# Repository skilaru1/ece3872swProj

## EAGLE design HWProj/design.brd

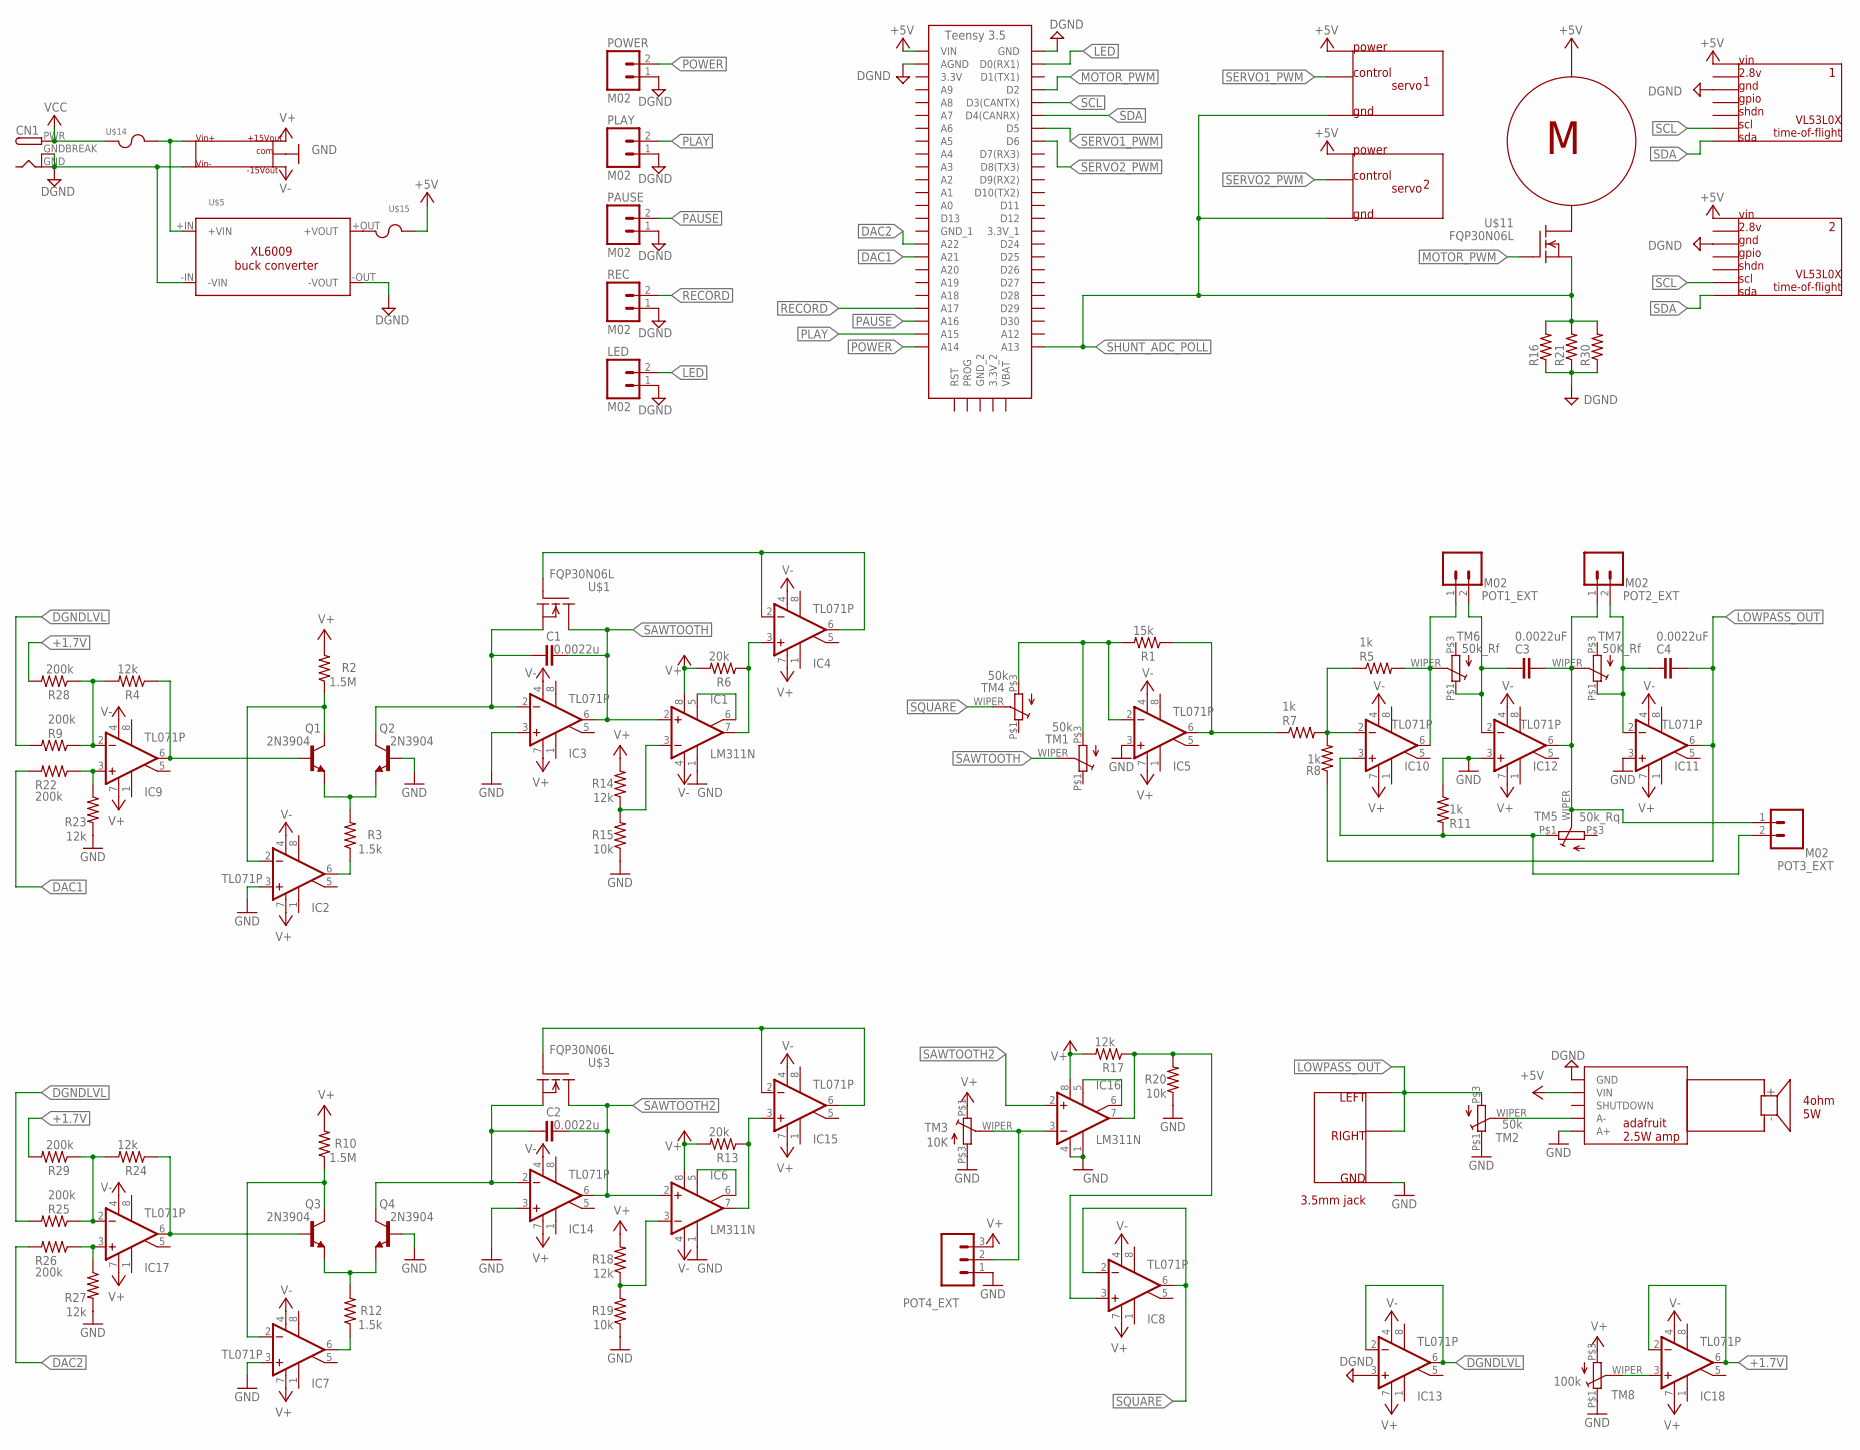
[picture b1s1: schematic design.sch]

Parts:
C1, C2: 0.0022u; CAP-PTH-5MM
C3, C4: 0.0022uF; CAP-PTH-5MM
CN1: DCBARRELPTH; DCJACK_2MM_PTH
IC1, IC6, IC16: LM311N; DIL08
IC2, IC3, IC4, IC5, IC7, IC8, IC9, IC10, IC11, IC12, IC13, IC14, IC15, IC17, IC18: TL071P; DIL08
LED: M02; 1X02
PAUSE: M02; 1X02
PLAY: M02; 1X02
POT1_EXT, POT2_EXT, POT3_EXT: M02; 1X02
POT4_EXT: M03; 1X03
POWER: M02; 1X02
Q1, Q2, Q3, Q4: 2N3904; TO92
R1: 15k; AXIAL-0.3
R2, R10: 1.5M; AXIAL-0.3
R3, R12: 1.5k; AXIAL-0.3
R4, R14, R17, R18, R23, R24, R27: 12k; AXIAL-0.3
R5, R7, R8, R11: 1k; AXIAL-0.3
R6, R13: 20k; AXIAL-0.3
R9, R22, R25, R26, R28, R29: 200k; AXIAL-0.3
R15, R19, R20: 10k; AXIAL-0.3
R16, R21, R30: RESISTORAXIAL-0.3; AXIAL-0.3
REC: M02; 1X02
TM1, TM2, TM4: 50k; 3386_TRI
TM3: 10K; 3386_TRI
TM5: 50k_Rq; 3386_TRI
TM6: 50k_Rf; 3386_TRI
TM7: 50K_Rf; 3386_TRI
TM8: 100k; 3386_TRI
U$1, U$3, U$11: FQP30N06L; TO-220
U$2: PAM8302A_ADAFRUIT
U$4: TEENSY_3.5_EXT
U$5: DC/DC-STEP-DOWN-XL6009; DC/DC-STEP-UP-XL6009
U$6: 3.5MM_AUDIO_JACK
U$7: +/-15V_BOOST_CONVERTER
U$8, U$9: SERVO_3PIN_HEADER
U$10: 3872_MOTOR
U$12, U$13: VL53L0X
U$14, U$15: FUSE_5X20MM; 0751.0110

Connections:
+1.7V: IC18.2 (-IN), IC18.6 (OUT), R28.P$2 (2), R29.P$2 (2)
+5V: U$2.VIN, U$4.VIN, U$8.POWER, U$9.POWER, U$10.+, U$12.VIN, U$13.VIN, U$15.R1 (2), U$15.R2 (2)
BANDPASS_OUT: C3.1, IC12.6 (OUT), POT2_EXT.1, POT3_EXT.1, TM5.WIPER (S), TM7.WIPER (S)
COMP_SQ_OUT: IC8.3 (+IN), IC16.7 (OUT), R17.P$1 (1), R20.P$2 (2)
DAC1: R22.P$2 (2), U$4.A21
DAC2: R26.P$2 (2), U$4.A22
DGND: CN1.GND, CN1.GNDBREAK, IC13.3 (+IN), LED.1, PAUSE.1, PLAY.1, POWER.1, R16.P$1 (1), R21.P$1 (1), R30.P$1 (1), REC.1, U$2.GND, U$4.AGND, U$4.GND, U$5.-IN (-VIN), U$5.-OUT (-VOUT), U$7.1, U$12.GND, U$13.GND
DGNDLVL: IC13.2 (-IN), IC13.6 (OUT), R9.P$2 (2), R25.P$2 (2)
GND: IC1.1 (GND), IC2.3 (+IN), IC3.3 (+IN), IC5.3 (+IN), IC6.1 (GND), IC7.3 (+IN), IC11.3 (+IN), IC12.3 (+IN), IC14.3 (+IN), IC16.1 (GND), IC16.4 (V-), POT4_EXT.1, Q2.2 (B), Q4.2 (B), R11.P$1 (1), R15.P$1 (1), R19.P$1 (1), R20.P$1 (1), R23.P$2 (2), R27.P$2 (2), TM2.P$1 (E), TM3.P$3 (A), TM8.P$1 (E), U$2.A+, U$6.GND, U$7.7
HIGHPASS_OUT: IC10.6 (OUT), POT1_EXT.1, R5.P$2 (2), TM6.WIPER (S)
INPUT2: IC5.6 (OUT), R1.P$1 (1), R7.P$1 (1)
LED: LED.2, U$4.D0(RX1)
LOWPASS_OUT: C4.1, IC11.6 (OUT), R8.P$1 (1), TM2.P$3 (A), U$6.L, U$6.R
MOTOR_PWM: U$4.D2, U$11.1 (G)
unnamed: TM2.WIPER (S), U$2.A-
unnamed: Q1.3 (E), Q2.3 (E), R3.P$2 (2)
unnamed: Q3.3 (E), Q4.3 (E), R12.P$2 (2)
unnamed: IC18.3 (+IN), TM8.WIPER (S)
unnamed: IC2.6 (OUT), R3.P$1 (1)
unnamed: IC1.7 (OUT), IC4.3 (+IN), R6.P$1 (1)
unnamed: C1.1, IC3.2 (-IN), Q2.1 (C), U$1.3 (S)
unnamed: IC6.7 (OUT), IC15.3 (+IN), R13.P$1 (1)
unnamed: IC1.5 (ON), IC1.6 (ON/STR)
unnamed: IC4.2 (-IN), IC4.6 (OUT), U$1.1 (G)
unnamed: IC17.3 (+IN), R26.P$1 (1), R27.P$1 (1)
unnamed: IC2.2 (-IN), Q1.1 (C), R2.P$1 (1)
unnamed: IC7.6 (OUT), R12.P$1 (1)
unnamed: C2.1, IC14.2 (-IN), Q4.1 (C), U$3.3 (S)
unnamed: IC6.5 (ON), IC6.6 (ON/STR)
unnamed: IC15.2 (-IN), IC15.6 (OUT), U$3.1 (G)
unnamed: IC16.5 (ON), IC16.6 (ON/STR)
unnamed: IC10.2 (-IN), R5.P$1 (1), R7.P$2 (2), R8.P$2 (2)
unnamed: IC17.6 (OUT), Q3.2 (B), R24.P$1 (1)
unnamed: C3.2, IC12.2 (-IN), POT1_EXT.2, TM6.P$1 (E)
unnamed: IC7.2 (-IN), Q3.1 (C), R10.P$1 (1)
unnamed: C4.2, IC11.2 (-IN), POT2_EXT.2, TM7.P$1 (E)
unnamed: IC6.3 (-IN), R18.P$1 (1), R19.P$2 (2)
unnamed: IC1.3 (-IN), R14.P$1 (1), R15.P$2 (2)
unnamed: IC10.3 (+IN), POT3_EXT.2, R11.P$2 (2), TM5.P$1 (E)
unnamed: IC16.3 (-IN), POT4_EXT.2, TM3.WIPER (S)
unnamed: IC17.2 (-IN), R24.P$2 (2), R25.P$1 (1), R29.P$1 (1)
unnamed: IC5.2 (-IN), R1.P$2 (2), TM1.P$3 (A), TM4.P$3 (A)
unnamed: U$5.+IN (+VIN), U$7.2, U$14.R1 (2), U$14.R2 (2)
unnamed: IC9.2 (-IN), R4.P$2 (2), R9.P$1 (1), R28.P$1 (1)
unnamed: IC9.3 (+IN), R22.P$1 (1), R23.P$1 (1)
unnamed: U$5.+OUT (+VOUT), U$15.L1 (1), U$15.L2 (1)
unnamed: U$10.-, U$11.2 (D)
PAUSE: PAUSE.2, U$4.A16
PLAY: PLAY.2, U$4.A15
POWER: POWER.2, U$4.A14
RECORD: REC.2, U$4.A17
SAWTOOTH: C1.2, IC1.2 (+IN), IC3.6 (OUT), TM1.WIPER (S), U$1.2 (D)
SAWTOOTH2: C2.2, IC6.2 (+IN), IC14.6 (OUT), IC16.2 (+IN), U$3.2 (D)
SCL: U$4.D3(CANTX), U$12.SCL, U$13.SCL
SDA: U$4.D4(CANRX), U$12.SDA, U$13.SDA
SERVO1_PWM: U$4.D5, U$8.CONTROL
SERVO2_PWM: U$4.D6, U$9.CONTROL
SHUNT_ADC_POLL: R16.P$2 (2), R21.P$2 (2), R30.P$2 (2), U$4.A13, U$8.GND, U$9.GND, U$11.3 (S)
SIGNAL1: IC9.6 (OUT), Q1.2 (B), R4.P$1 (1)
SQUARE: IC8.2 (-IN), IC8.6 (OUT), TM4.WIPER (S)
V+: IC1.8 (V+), IC2.7 (V+), IC3.7 (V+), IC4.7 (V+), IC5.7 (V+), IC6.8 (V+), IC7.7 (V+), IC8.7 (V+), IC9.7 (V+), IC10.7 (V+), IC11.7 (V+), IC12.7 (V+), IC13.7 (V+), IC14.7 (V+), IC15.7 (V+), IC16.8 (V+), IC17.7 (V+), IC18.7 (V+), POT4_EXT.3, R2.P$2 (2), R6.P$2 (2), R10.P$2 (2), R13.P$2 (2), R14.P$2 (2), R17.P$2 (2), R18.P$2 (2), TM3.P$1 (E), TM8.P$3 (A), U$7.6
V-: IC1.4 (V-), IC2.4 (V-), IC3.4 (V-), IC4.4 (V-), IC5.4 (V-), IC6.4 (V-), IC7.4 (V-), IC8.4 (V-), IC9.4 (V-), IC10.4 (V-), IC11.4 (V-), IC12.4 (V-), IC13.4 (V-), IC14.4 (V-), IC15.4 (V-), IC17.4 (V-), IC18.4 (V-), U$7.8
VCC: CN1.PWR, U$14.L1 (1), U$14.L2 (1)

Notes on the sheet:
4ohm 5W
3.5mm jack

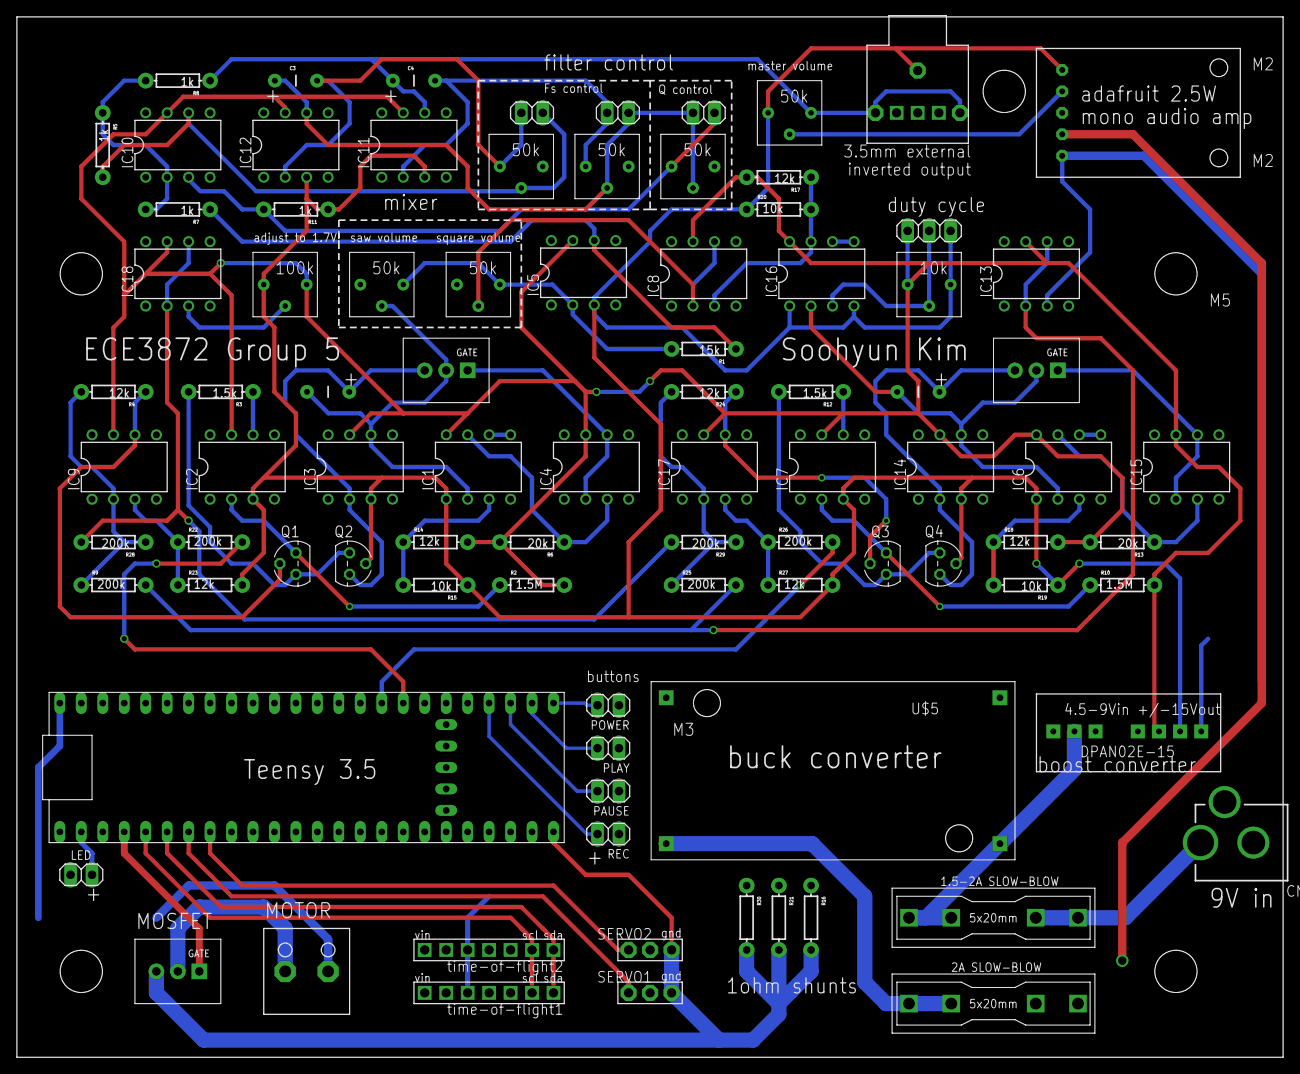
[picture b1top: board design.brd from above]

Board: 2 copper layers, 149.8 x 123.1 mm, 89 parts (0 on the bottom side), 63 nets.

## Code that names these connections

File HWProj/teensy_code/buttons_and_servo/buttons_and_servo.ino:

#include <Servo.h>
#include "Adafruit_VL53L0X.h"

bool power = true;     // on/off boolean NOTE: in production, set to false. Set to true for debugging.
bool play = false;     // play/pause boolean
int recSquare[10];     // square sound recording
int recTriangle[10];   // triangle sound recording
int ledPin = 0;        // recording light
int ToFLeftPin = A21;  // ToF Left DAC Pin
int ToFRightPin = A22; // ToF Right DAC Pin
int recSize = 0;       // count for number of notes in recording
int DCMotor = 32;      // Pin for DC Motor based on schematic
int rangeMult = 1;     // 1 for about a meter of range playability, 2 for about half a meter, 3 for a third, etc.
Servo laser1;          // laser servo 1
Servo laser2;          // laser servo 2

Adafruit_VL53L0X lox = Adafruit_VL53L0X(); // Left ToF Sensor

// pin setup loop
void setup()   {                
  Serial.begin(115200);

    // wait until serial port opens for native USB devices, remove in final code
  while (! Serial) {
    delay(1);
  }
      Serial.println("GROUP V Loading...");
       if (!lox.begin()) {
       Serial.println(F("Failed to boot the VL53L0X"));
         while(1);
       }
      //Note: default I2C address is 0x29. We can use lox.begin(0x30) to set another address for the second ToF sensor.

  analogWriteResolution(12); // allows for 4092 bits of resolution as opposed to 255. LEDs are set with HIGH which should adjust to 4092.
      
  
  // LOW == off, HIGH == on
  pinMode(33, INPUT_PULLUP);    // power on/off
  pinMode(34, INPUT_PULLUP);    // play
  pinMode(35, INPUT_PULLUP);    // pause
  pinMode(36, INPUT_PULLUP);    // record
  pinMode(A12, INPUT_PULLUP);    // overcurrent resistor
  pinMode(ledPin, OUTPUT);      // recording light
  pinMode(ToFLeftPin, OUTPUT);  // left ToF sensor
  pinMode(ToFRightPin, OUTPUT); // right ToF sensor

  pinMode(DCMotor, OUTPUT);       // DC motor
  
  // Laser servos
  laser1.attach(5);
  laser2.attach(6);
}


// Function returns the data from our ToF Sensor


// Function to change PWM based on desired DC motor speed
void spinPyramid(bool spin, int d) {
  if (spin) {
    analogWrite(DCMotor, HIGH);
    delay(d);
    analogWrite(DCMotor, LOW);
    delay(d);
  }
}


// Function to record sound
void startRecording() {
  // reset saved recording
  recSquare[10] = {};         // warning flagged here; possible error?
  recTriangle[10] = {};       // warning flagged here; possible error?
  recSize = 0;
  
  // wait until record button is pressed again
  while (digitalRead(10) == LOW || recSize < 10) {
    recSquare[recSize] = 1; // TODO: Change to input of tof sensor
    recTriangle[recSize] = 1; // TODO: Change to input of other tof sensor
    recSize ++;
  }
  digitalWrite(ledPin, LOW); // turn recording light off
}


// Function to play recorded sound
void playSound() {

  float angle1, angle2;

  spinPyramid(1, 16);
  for (int i = 0; i < recSize; i++) {

      // Turn on speaker and output recorded sound
      // TODO

      // Laser 1 movement
       angle1 = (recSquare[i] % 90) - 90;
       laser1.write(angle1);

      // Laser 2 movement
       angle2 = (recTriangle[i] % 90) - 90;
       laser2.write(angle2);

       // Check for pause during play function
       if (digitalRead(9) == HIGH) {
         play = false;
       }
  }
  spinPyramid(0, 0);
  play = false; // stop play after goes through recording once
}


// Function to play sound instantly given
// movement over the tof sensors
void normalPlay() {

  int measureL; //intermediate measurment
  float calcL;  //intermediate calculation
  
  VL53L0X_RangingMeasurementData_t measure; // create a measure object for our ToF sensor
  
  Serial.print("Left ToF is measuring... ");
  lox.rangingTest(&measure, false); // false argument just supresses debug info
  
  if (measure.RangeStatus != 4) {  // phase failures have incorrect data
    Serial.print("Distance (mm): "); 
    measureL = measure.RangeMilliMeter * rangeMult; //adjusts the range to make playing easier
    calcL = (measureL/1200.0)*4092.0; // Range ends around 1100mm, mod as a safeguard, adjust to DAC range
    
    if (calcL>4092){ calcL=4092;}
    Serial.println(calcL); //Serial.println(measure.RangeMilliMeter);
  } else {
    Serial.println(" out of range ");
  }
  
  int tof_left = (int)calcL;  // cast back to an int for the analogWrite
  int tof_right = 0; // TODO: implement right ToF
  
  analogWrite(ToFLeftPin, tof_left); // write value to Left DAC
  // analogWrite(ToFRightPin, tof_right); //write value to Right DAC

  // Change laser direction
  float angle1 = (tof_left % 90) - 90;
  laser1.write(angle1);
  float angle2 = (tof_right % 90) - 90;
  laser2.write(angle2);

  // spins pyramid
  spinPyramid(1, 16);
  delay(100); // for smoothness
}

void loop()                     
{
  

    
  // only use this loop if the power button has been pressed and is on
  while (power == true) {

   // Comment out below because the voltage is default High
   // if(analogRead(A12)>800){   // Check for overcurrent using pin A12. analogRead returns a number from 0-1023
   // power = false;
   // break; // exit the loop
   // } 

    // Play sound from recording
    if (play == true) {
      playSound();
    } else {
      normalPlay();
    }

    // Play button
    if (digitalRead(8) == HIGH) {
      play = true;
    }

    // Pause button
    if (digitalRead(9) == HIGH) {
      spinPyramid(0,0);
      play = false;
    }

    // Record button
    if (digitalRead(10) == HIGH) {
      delay(1000);  // wait 1 sec to ensure button is released
      digitalWrite(ledPin, HIGH); // turn recording light on
      startRecording();
      spinPyramid(0,0);
    }

    // Turn power off
    if (digitalRead(7) == HIGH) {
      power = false;
      spinPyramid(0,0);
    }
  }

  // Turn power on
  if (digitalRead(7) == HIGH) {
    power = true;
    spinPyramid(0,0);
  }

}

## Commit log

2020-01-26 starter
2020-01-27 move functions implemented
2020-01-30 includes compiled code with states from state machine, not yet tested
2020-01-30 new testing
2020-01-30 working on turn right
2020-01-30 right turn functioning
2020-02-04 Left turn not working
2020-02-04 Work on last state (E)
2020-02-05 weird stopping thing
2020-02-05 fixed curr zero issue
2020-02-05 everything works but the black line
2020-02-06 Work on last turn part
2020-02-07 final version
2020-02-25 added schematic
2020-02-25 added eagle custom parts for design
2020-02-26 1st order vcf and 2nd order manual filter added (unsimulated)
2020-02-27 tested two-pole filter circuit, determined r/c val
2020-02-27 removed extraneous components for analog--complete
2020-02-28 incorporated adafruit amp, minor revisions
2020-03-04 begin designing entire schematic, added power
2020-03-04 changed value of volume control pot at speaker stage to 50k
2020-03-04 corrected teensy vin
2020-03-06 added teensy 3.5 DAC test code
2020-03-07 completed initial design for testing, revisions
2020-03-09 added 3.5mm jack
2020-03-09 fixed ground ref for amp, replaced boost converter
2020-03-10 added board rev0
2020-03-10 revised board rev0.2
2020-03-11 added motor, sensors, and servos--board rev1
2020-03-11 silkscreen cleanup, tested square generation
2020-03-12 added fuses, shunt system, finalized board rev1.1
2020-03-12 revised teensy test code to light LED
2020-04-02 Added code for button and servo functions
2020-04-03 attempted integration of buttons and servos
2020-04-03 minor commit; added silkscreen text
2020-04-04 post-prototype evaluation revisions
2020-04-06 added DC Motor functionality
2020-04-10 Left ToF and Overcurrent Added
    Need to work with Soohyun on the overcurrent, right now I'm reading an analog voltage from A12 assuming we'd put a resistor on the other side of the pin. Outside of that, all of the ToF I2C code work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
2020-04-10 Fixed the analogRead pin
